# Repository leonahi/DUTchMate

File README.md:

<p align="center">
  Connect your coding agent to your embedded device.
</p>

# DUTchMate

DUTchMate gives your coding agent access to UART logs, firmware commands, and
configured reset and boot controls through MCP. Your agent can investigate
device behavior alongside your source code, using recorded evidence.

Use your coding agent's existing model. The separate DUTchMate Debug Agent
package is not required.

## 1. Install DUTchMate

Requires **Python 3.10+** and **uv**:

```bash
uv tool install dutchmate==0.2.0
```

If the installed commands are not on your PATH, run `uv tool update-shell` and
reopen your terminal. See the [v0.2.0 release notes](docs/releases/v0.2.0.md)
for upgrade guidance, or the [setup guide](docs/developer_guide.md#local-setup)
to run from a repository checkout.

## 2. Connect your device

| Connection | Available capabilities |
|---|---|
| TTL USB-to-UART adapter (Basic) | UART logs and optional firmware commands |
| RP2350 Pico 2 Debug Helper (Enhanced) | UART plus configured reset, boot and GPIO control |

Connect your adapter and configure the matching baud rate and wiring. See the
[setup guide](docs/developer_guide.md#local-setup) for configuration. Replace
`YOUR_UART_PORT` with your adapter's actual serial port:

```bash
dutchmate start --backend basic --serial-port YOUR_UART_PORT
dutchmate status
```

For the Debug Helper, use `dutchmate start --backend enhanced` instead. Follow
the [wiring guide](hardware/firmware/rp2350_debug_helper/README.md#revision-a-mapping)
to connect its DUT_VIO reference to the DUT's logic supply.

## 3. Connect your coding agent

Find the MCP launcher's absolute path:

```bash
command -v dutchmate-mcp
```

Register a local MCP server in your coding agent with these settings:

| Setting | Value |
|---|---|
| Name | `dutchmate` |
| Transport | `stdio` |
| Command | The absolute launcher path printed above |
| Arguments | `--service-url http://127.0.0.1:2040` |

See the [agent-specific configuration examples](docs/developer_guide.md#register-mcp-with-a-coding-agent)
for the format your host expects. Your coding agent launches the MCP process.
**The Device Core Service must already be running; MCP does not start it.**

Verify that the agent lists the DUTchMate tools, then ask it to check the device
connection before debugging.

## 4. Start debugging

Try these prompts in your coding agent:

> Check the device connection and summarize the latest UART logs.

> Observe UART for 15 seconds and identify errors or unexpected behavior.

> Investigate this boot failure using the UART evidence and this repository.
> Propose a fix, and ask before resetting the board or sending commands.

DUTchMate records UART continuously while the service owns the connection, so
your agent can retrieve evidence between requests. Sending commands requires
UART TX to be enabled; reset and boot actions require configured control mappings.

When finished:

```bash
dutchmate stop
```

## Further information

- [Configuration and CLI workflows](docs/developer_guide.md) — also run `dutchmate --help`.
- [Debug Helper wiring and firmware](hardware/firmware/rp2350_debug_helper/README.md).
- [Milestone overview and validation boundaries](docs/development_status.md).
- [Contributing](CONTRIBUTING.md) and the [documentation index](docs/README.md).

## Licensing

Software, firmware and documentation use the [MIT License](LICENSE), unless
otherwise noted. DUTchMate-authored hardware design files under `hardware/pcb/`
use [CERN-OHL-P-2.0](LICENSES/CERN-OHL-P-2.0.txt). Legacy EAGLE and third-party
assets retain their existing terms; see [LICENSE.md](LICENSE.md) and
[third-party notices](THIRD_PARTY_NOTICES.md).

The DUTchMate name, logo and branding are excluded from these grants; they do
not authorize presenting derivative products as official DUTchMate products.
Contributions require DCO 1.1 sign-off; see [CONTRIBUTING.md](CONTRIBUTING.md).

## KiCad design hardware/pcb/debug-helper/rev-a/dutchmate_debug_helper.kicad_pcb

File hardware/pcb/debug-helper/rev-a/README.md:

# Debug Helper Revision A — KiCad source

This directory contains the current authoritative Rev-A KiCad design source
for the DUTchMate Debug Helper. The historical EAGLE prototype design record
is preserved separately under [legacy-eagle](../legacy-eagle/revision_a.md).
Its component references and connector assignments do not define this KiCad
implementation.

## Design sources

- `dutchmate_debug_helper.kicad_pro`: KiCad project and check settings.
- `dutchmate_debug_helper.kicad_sch`: schematic and embedded symbol definitions.
- `dutchmate_debug_helper.kicad_pcb`: board source.
- `dutchmate_debug_helper.kicad_dru`: project design rules.
- `libraries/symbols/dutchmate.kicad_sym`: project-owned logic and analog-switch
  symbol definitions, resolved through `sym-lib-table` using `${KIPRJMOD}`.
- `libraries/symbols/third_party/snapeda.kicad_sym` and
  `libraries/footprints/third_party/snapeda.pretty/`: imported TPD4E05U06DQAR
  symbol and footprint, resolved through `sym-lib-table` and `fp-lib-table`.

The sources use KiCad 10 format. Standard KiCad symbols and footprints must be
installed alongside the project-owned library. Keep editable sources and any
reviewed manufacturing outputs in version control; local settings, locks,
autosaves, backups, and scratch exports are ignored.

## Electrical architecture and agreed corrections

The helper uses a non-wireless Raspberry Pi Pico 2 / RP2350 module (`A1`),
with a 3.3 V helper domain, a DUT-supplied `DUT_VIO` reference of 1.8–5.0 V,
and common ground. `DUT_VIO` supplies the interface circuitry; it is not an
output for powering the DUT.

| Block | KiCad implementation |
|---|---|
| Four control outputs | `U1 SN74LV4T125`, VCC=`DUT_VIO`; `U7/U8 SN74LVC2G06` open-drain enable drivers powered by `+3.3V` |
| Control data defaults | `R14–R17`, 10 kΩ to GND on `DBG_CTRL_DATA0–3` |
| Control enable defaults | `R1–R4`, 4.7 kΩ to GND; active-low `DBG_CTRL_OE0_N–3_N` pulled to `DUT_VIO` by `R7/R6/R9/R8`, respectively, each 4.7 kΩ |
| Four event inputs | `U5 TXU0104PWR`, VCCA=`DUT_VIO`, VCCB=`+3.3V`; `R5=4.7 kΩ` pulls `DBG_INPUT_IF_EN` low |
| UART | `U2 TXU0202DCUR`, VCCA=`+3.3V`, VCCB=`DUT_VIO`; `R12=4.7 kΩ` pulls `DBG_UART_IF_EN` low |
| Series resistance | `RN3/RN4=180 Ω` for control/event channels; `RN5=22 Ω` for UART |
| Protection | `U9 TPD4E05U06DQAR` on connector-side controls, `U4` on connector-side events/UART, `D1` between `DUT_VIO` and GND |

The 4.7 kΩ enable pull-downs retain compatibility with older RP2350 A2
silicon; the design does not require A4-only modules. Control data pull-downs
define the buffer inputs while Pico GPIOs are undriven. The independent `/OE`
paths determine DUT-facing Hi-Z, including open-drain release. Push-pull and
open-drain control modes still require the appropriate firmware data/enable
sequence.

### Hardware-defined DUT_VIO sense isolation

`U3 TMUX2819DSGR` is connected as follows:

| Pin | Connection |
|---|---|
| 1, SA | `DUT_VIO` |
| 2, NC | GND, as specified by the datasheet |
| 3, EN; 8, VDD | `+3.3V`, with `C16=100 nF` between VDD and GND |
| 4, GND; 9, exposed pad | GND |
| 5, SB | Intentionally unconnected |
| 6, D | `R10` divider input |
| 7, SEL | GND |

With helper power present, EN high and SEL low select SA. With VDD absent,
the switch provides powered-off isolation within its specified leakage limits.
No firmware GPIO controls this isolation. The selected switch supports DUT
signals above its 3.3 V supply within the specified signal range. See the
[TMUX2819 datasheet](https://www.ti.com/lit/ds/symlink/tmux2819.pdf).

The divider remains `R10=47 kΩ` and `R11=47 kΩ`, with `C7=10 nF` from
`DUT_VIO_SENSE` to `GNDA`. `R11` also returns to `GNDA`, connected to the
Pico's AGND pin 33. `DUT_VIO_SENSE` reaches GP28/ADC2, module pin 34. The Pico
module supplies the internal analog/common-ground connection; these are
distinct carrier-board net names, not galvanically isolated domains.

Normal helper startup disables GP28 digital input/output and internal pulls,
then releases the RP2350 pad-isolation latch so the reset pull cannot load the
divider. GP28 ADC sensing remains unimplemented: there is no ADC channel setup
or sampled voltage monitoring. The optional
[pad readback](../../../firmware/rp2350_debug_helper/README.md#gp28-sense-pin-initialization)
reports control bits without implementing sensing. Future ADC use must retain
the appropriate analog pin configuration. MCU pad isolation and U3's
hardware-defined powered-off isolation are separate paths; neither the
schematic nor the switch enable establishes firmware voltage measurements.

### UART receive bias

```text
J1.7 / DUT_UART_TX -- RN5A 22 Ω (pad 4 → pad 1) -- U2.B2 (pin 1)
                                                     |
                                                 R13 10 kΩ
                                                     |
                                                  DUT_VIO
```

`R13` is on the translator-input side of the series resistor, on exported net
`Net-(RN5A-R1.1)`. It references `DUT_VIO`, not fixed `+3.3V`. The translated
output is `DBG_UART_RX`, from U2 pin 4 to Pico GP1. The opposite direction is
Pico GP0 / `DBG_UART_TX` to U2 pin 5, U2 pin 8 through RN5B, then
`DUT_UART_RX` at J1 pin 8. Both UART directions share U2 OE; software TX
permission does not provide independent electrical TX isolation.

## DUT connector and interface requirements

The single 2×8 `J1` is the authoritative Rev-A DUT connector. Direct legacy
EAGLE harness compatibility is not required; any legacy connection requires
an external adapter cable.

| J1 pin(s) | Net(s) | Direction relative to helper |
|---|---|---|
| 1, 2 | GND | Common |
| 3, 4, 5, 6 | `DUT_CTRL0`, `DUT_CTRL1`, `DUT_CTRL2`, `DUT_CTRL3` | Outputs |
| 7 | `DUT_UART_TX` | Input from DUT TX |
| 8 | `DUT_UART_RX` | Output to DUT RX |
| 9, 10 | `DUT_EVENT2`, `DUT_EVENT3` | Inputs |
| 11, 12 | `DUT_EVENT0`, `DUT_EVENT1` | Inputs |
| 13 | GND | Common |
| 14 | `DUT_VIO` | Reference/supply input from DUT |
| 15, 16 | GND | Common |

`DUT_CTRL0–3` must remain within the `DUT_VIO` voltage domain. In particular,
a released externally pulled-up control signal must not be pulled above
`DUT_VIO`. U1 remains the selected SN74LV4T125. Control outputs drive logic
inputs, not DUT supply loads.

`DUT_EVENT0–3` intentionally have **no helper-side pull-ups**. These temporary
debugging inputs are normally driven by spare DUT GPIOs. The DUT/developer
must supply valid logic levels. Open-drain/open-collector outputs require a
DUT-side pull-up, including an MCU internal pull-up where its electrical and
timing performance is adequate. A floating event input is not a valid event
source.

## Validation lifecycle and evidence boundaries

The KiCad Rev-A schematic/source review is complete. PCB layout, routing,
fabrication preparation, DFM checks, Gerber review and manufacturing submission
are handled manually by the hardware designer outside the coding-agent
workflow. No further repository-driven PCB/DFM review task or acceptance gate
is planned before fabrication. Source-review completion does not establish
hardware acceptance, fabrication acceptance, production readiness or Phase 1B
acceptance.

Formal hardware validation of this corrected design begins only after
manufactured KiCad Rev-A PCBs are physically available. Each manufactured-board
validation campaign must record its own board/assembly configuration, wiring,
firmware, methods and observed results. Use the same broad categories as the
historical Rev-A work, adapted to this implementation, where applicable:

- Visual inspection, board assembly/continuity checks and firmware/board
  pin-mapping consistency.
- Power rails, `DUT_VIO` checks and operation across the supported voltage range.
- Debugger-powered/DUT-unpowered and DUT-powered/debugger-unpowered behavior,
  including powered-off back-power/leakage checks.
- `U3 TMUX2819` isolation of the `DUT_VIO` sense path and its divider/filter.
- Control-channel safe startup/Hi-Z, open-drain assertion/release and push-pull
  output levels.
- Event-input behavior with valid DUT-provided levels and any DUT-side pull-ups
  required for open-drain/open-collector signals.
- UART TX/RX functionality, the corrected after-RN5A `R13` pull-up, and UART
  signal-integrity/oscilloscope measurements.
- Hot-plug/unplug behavior and translator enable/disable sequencing.
- ESD/protection-path sanity checks where measurable, and Enhanced-backend HIL
  workflows relevant to the manufactured board.

These are future validation categories, not completed checks or new acceptance
criteria. Use applicable existing specifications and procedures for limits and
acceptance conditions; do not infer results or tolerances from source review.
The GP28 firmware limitation above and deferred EVENT capture must be respected
when defining what a physical run can demonstrate.

Adapt procedural references to the single 2×8 J1 pinout, current component/net
references and corrected circuit documented above. In particular, test the
after-RN5A `R13` pull-up at `U2.B2` to `DUT_VIO`; do not copy the historical
two-connector arrangement, historical R16 references or before-R16 rework
location into a KiCad-board procedure.

The three evidence scopes remain separate:

- Historical EAGLE [validation records](../../../validation/phase1_revision_a.md)
  establish evidence only for the actual EAGLE/as-built prototype, wiring,
  parts and firmware tested. They remain useful procedural/reference material.
  Their UART oscilloscope gap remains unresolved. The legacy board may still
  serve as a functional Enhanced HIL/development fixture under
  [Phase 1 specification §4.1](../../../../docs/specs/phase1_implementation_spec.md#41-software-sequencing-and-hardware-acceptance-boundaries);
  such use does not establish electrical acceptance. Current-board UART
  electrical follow-up belongs to the manufactured KiCad campaign above.
- The completed KiCad source review establishes that the corrected design
  source was reviewed; it is not physical-board validation.
- Future manufactured KiCad Rev-A validation supplies separate physical
  evidence required for that board. Historical acceptance is not inherited.

Current progress and the next formal hardware-validation step belong in
[development status](../../../../docs/development_status.md); dated decisions
and source-check results belong in
[development history](../../../../docs/development_history.md).

## Licensing and provenance

DUTchMate-authored design source, project metadata, and the project-owned
symbol definitions in this directory are licensed under
[CERN-OHL-P-2.0](../../../../LICENSES/CERN-OHL-P-2.0.txt).

Embedded and referenced third-party symbols, footprints, models, and other CAD
assets retain their existing terms. Standard KiCad library data retains its
upstream license and design exception. This grant does not establish ownership
of imported assets or complete the manufacturing-output provenance audit.
Do not copy embedded EAGLE libraries or other third-party CAD assets into this
project without checking their provenance and terms. See the
[hardware scope](../../README.md) and
[third-party notices](../../../../THIRD_PARTY_NOTICES.md).

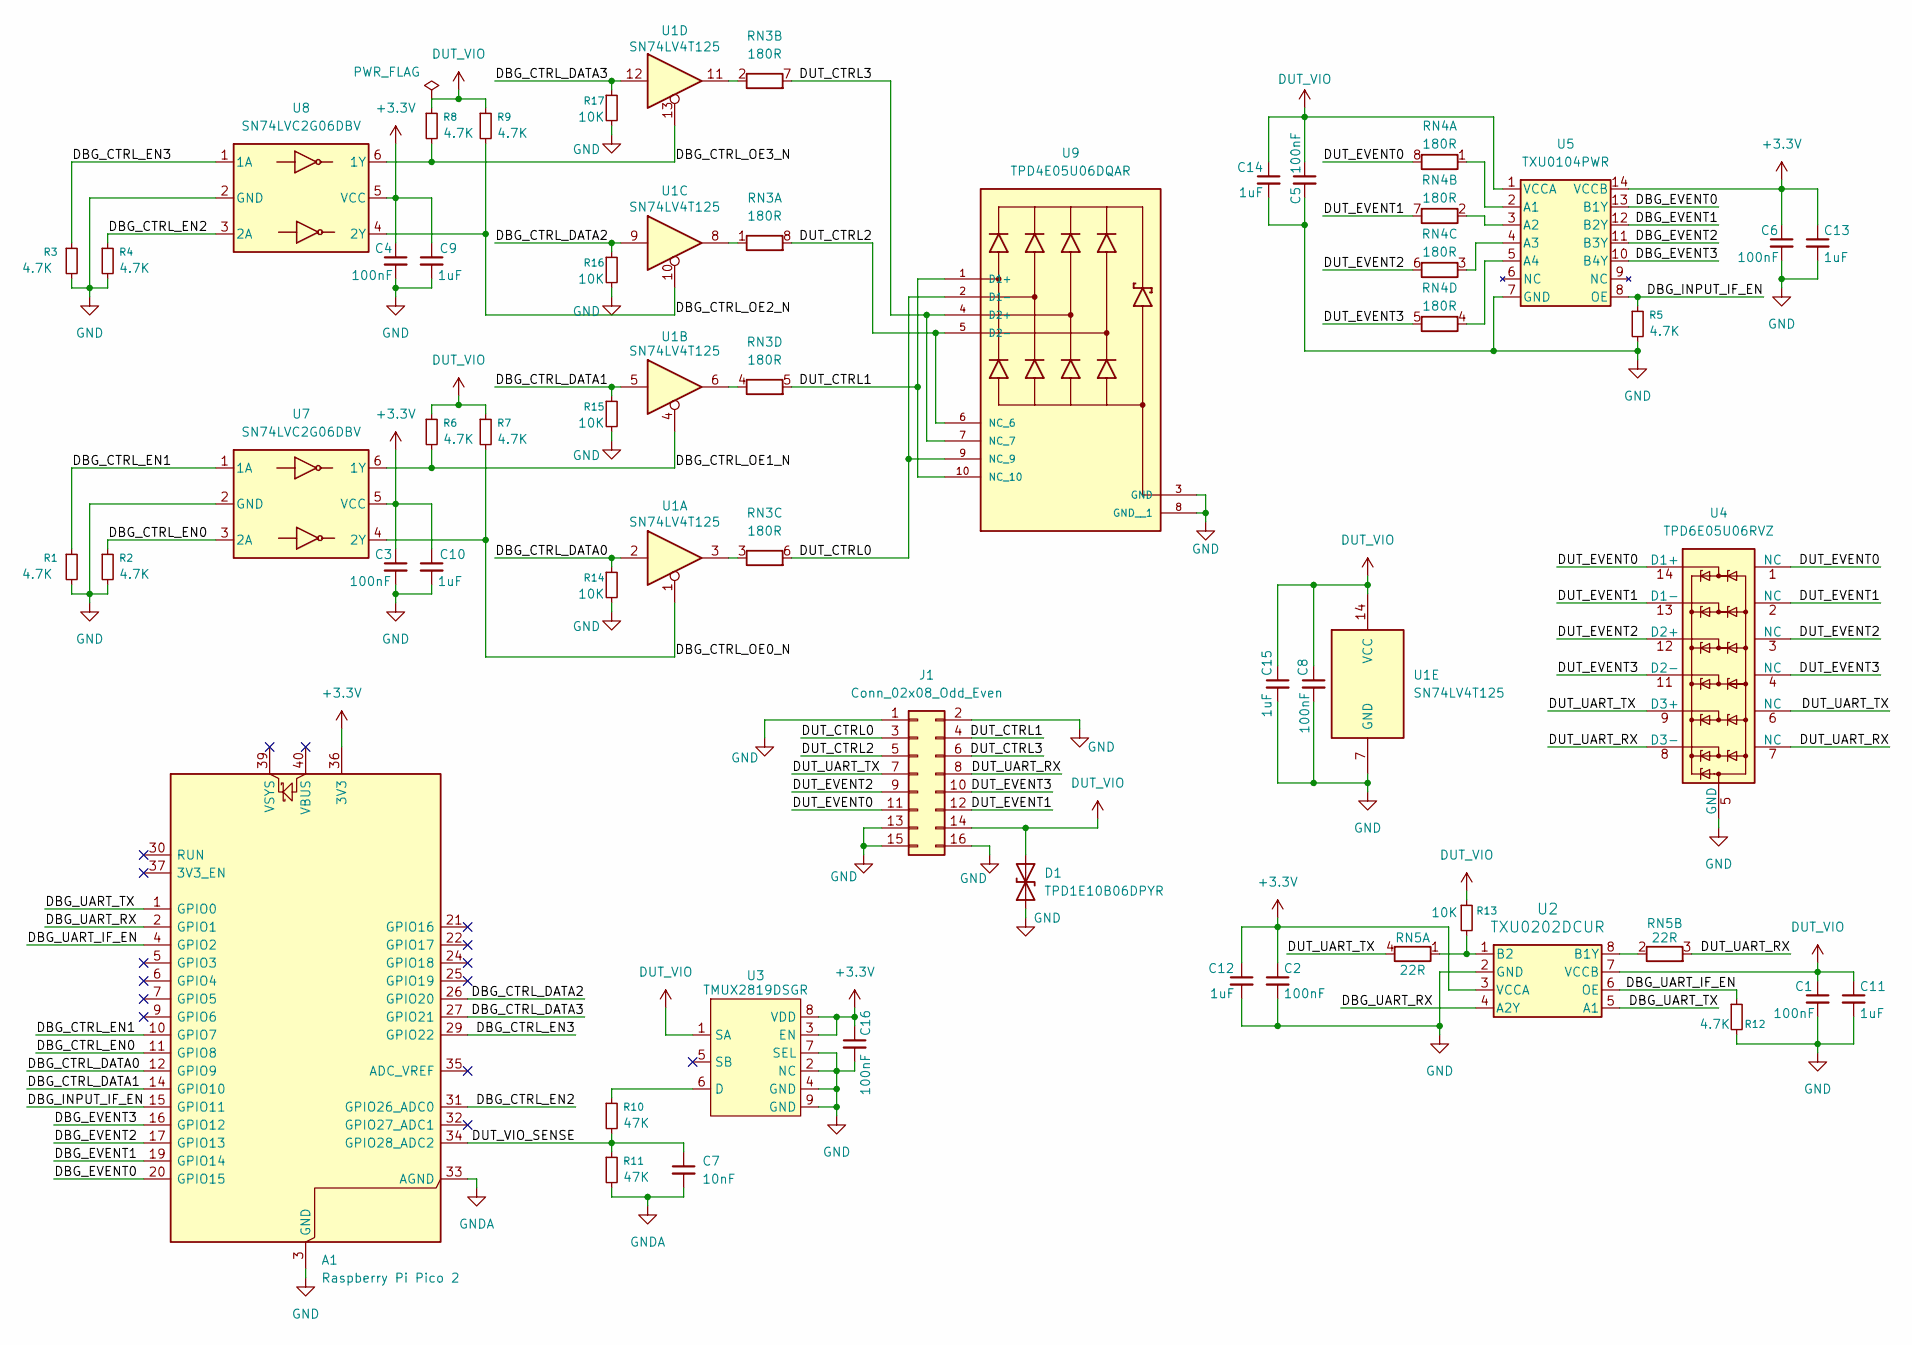
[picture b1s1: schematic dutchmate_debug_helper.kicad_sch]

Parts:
A1: Raspberry Pi Pico 2; RaspberryPi_Pico_Common_THT
C1, C2, C3, C4, C5, C6, C8, C16: 100nF; C_0603_1608Metric
C7: 10nF; C_0603_1608Metric
C9, C10, C11, C12, C13, C14, C15: 1uF; C_0603_1608Metric
D1: TPD1E10B06DPYR; Texas_DPY0002A_0.6x1mm_P0.65mm
J1: Conn_02x08_Odd_Even; PinHeader_2x08_P2.54mm_Vertical
R1, R2, R3, R4, R5, R6, R7, R8, R9, R12: 4.7K; R_0603_1608Metric
R10, R11: 47K; R_0603_1608Metric
R13, R14, R15, R16, R17: 10K; R_0603_1608Metric
RN3, RN4: 180R; R_Array_Concave_4x0603
RN5: 22R; R_Array_Concave_2x0603
U1: SN74LV4T125; TSSOP-14_4.4x5mm_P0.65mm
U2: TXU0202DCUR; VSSOP-8_2.3x2mm_P0.5mm
U3: TMUX2819DSGR; Texas_DSG0008A_WSON-8-1EP_2x2mm_P0.5mm_EP0.9x1.6mm
U4: TPD6E05U06RVZ; Texas_R-PUSON-N14
U5: TXU0104PWR; TSSOP-14_4.4x5mm_P0.65mm
U7, U8: SN74LVC2G06DBV; SOT-23-6
U9: TPD4E05U06DQAR; PARTREV N

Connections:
+3.3V: A1.36 (3V3), C2.1, C3.1, C4.1, C6.1, C9.1, C10.1, C12.1, C13.1, C16.1, U2.3 (VCCA), U3.3 (EN), U3.8 (VDD), U5.14 (VCCB), U7.5 (VCC), U8.5 (VCC)
/DBG_CTRL_DATA0: A1.12 (GPIO9), R14.1, U1.2
/DBG_CTRL_DATA1: A1.14 (GPIO10), R15.1, U1.5
/DBG_CTRL_DATA2: A1.26 (GPIO20), R16.1, U1.9
/DBG_CTRL_DATA3: A1.27 (GPIO21), R17.1, U1.12
/DBG_CTRL_EN0: A1.11 (GPIO8), R2.1, U7.3 (2A)
/DBG_CTRL_EN1: A1.10 (GPIO7), R1.1, U7.1 (1A)
/DBG_CTRL_EN2: A1.31 (GPIO26_ADC0), R4.1, U8.3 (2A)
/DBG_CTRL_EN3: A1.29 (GPIO22), R3.1, U8.1 (1A)
/DBG_CTRL_OE0_N: R7.2, U1.1, U7.4 (2Y)
/DBG_CTRL_OE1_N: R6.2, U1.4, U7.6 (1Y)
/DBG_CTRL_OE2_N: R9.2, U1.10, U8.4 (2Y)
/DBG_CTRL_OE3_N: R8.2, U1.13, U8.6 (1Y)
/DBG_EVENT0: A1.20 (GPIO15), U5.13 (B1Y)
/DBG_EVENT1: A1.19 (GPIO14), U5.12 (B2Y)
/DBG_EVENT2: A1.17 (GPIO13), U5.11 (B3Y)
/DBG_EVENT3: A1.16 (GPIO12), U5.10 (B4Y)
/DBG_INPUT_IF_EN: A1.15 (GPIO11), R5.1, U5.8 (OE)
/DBG_UART_IF_EN: A1.4 (GPIO2), R12.1, U2.6 (OE)
/DBG_UART_RX: A1.2 (GPIO1), U2.4 (A2Y)
/DBG_UART_TX: A1.1 (GPIO0), U2.5 (A1)
/DUT_CTRL0: J1.3, RN3.6 (R3.2), U9.2 (D1-), U9.9 (NC_9)
/DUT_CTRL1: J1.4, RN3.5 (R4.2), U9.1 (D1+), U9.10 (NC_10)
/DUT_CTRL2: J1.5, RN3.8 (R1.2), U9.5 (D2-), U9.6 (NC_6)
/DUT_CTRL3: J1.6, RN3.7 (R2.2), U9.4 (D2+), U9.7 (NC_7)
/DUT_EVENT0: J1.11, RN4.8 (R1.2), U4.1 (NC), U4.14 (D1+)
/DUT_EVENT1: J1.12, RN4.7 (R2.2), U4.2 (NC), U4.13 (D1-)
/DUT_EVENT2: J1.9, RN4.6 (R3.2), U4.3 (NC), U4.12 (D2+)
/DUT_EVENT3: J1.10, RN4.5 (R4.2), U4.4 (NC), U4.11 (D2-)
/DUT_UART_RX: J1.8, RN5.3 (R2.2), U4.7 (NC), U4.8 (D3-)
/DUT_UART_TX: J1.7, RN5.4 (R1.2), U4.6 (NC), U4.9 (D3+)
/DUT_VIO_SENSE: A1.34 (GPIO28_ADC2), C7.1, R10.2, R11.1
DUT_VIO: C1.1, C5.1, C8.1, C11.1, C14.1, C15.1, D1.2 (A2), J1.14, R6.1, R7.1, R8.1, R9.1, R13.1, U1.14 (VCC), U2.7 (VCCB), U3.1 (SA), U5.1 (VCCA)
GND: A1.3 (GND), A1.8 (GND), A1.13 (GND), A1.18 (GND), A1.23 (GND), A1.28 (GND), A1.38 (GND), C1.2, C2.2, C3.2, C4.2, C5.2, C6.2, C8.2, C9.2, C10.2, C11.2, C12.2, C13.2, C14.2, C15.2, C16.2, D1.1 (A1), J1.1, J1.2, J1.13, J1.15, J1.16, R1.2, R2.2, R3.2, R4.2, R5.2, R12.2, R14.2, R15.2, R16.2, R17.2, U1.7 (GND), U2.2 (GND), U3.2 (NC), U3.4 (GND), U3.7 (SEL), U3.9 (GND), U4.5 (GND), U4.10 (GND), U5.7 (GND), U7.2 (GND), U8.2 (GND), U9.3 (GND), U9.8 (GND__1)
GNDA: A1.33 (AGND), C7.2, R11.2
unnamed: RN3.1 (R1.1), U1.8
unnamed: RN3.2 (R2.1), U1.11
unnamed: RN3.3 (R3.1), U1.3
unnamed: RN3.4 (R4.1), U1.6
unnamed: RN4.1 (R1.1), U5.2 (A1)
unnamed: RN4.2 (R2.1), U5.3 (A2)
unnamed: RN4.3 (R3.1), U5.4 (A3)
unnamed: RN4.4 (R4.1), U5.5 (A4)
unnamed: R13.2, RN5.1 (R1.1), U2.1 (B2)
unnamed: RN5.2 (R2.1), U2.8 (B1Y)
unnamed: R10.1, U3.6 (D)

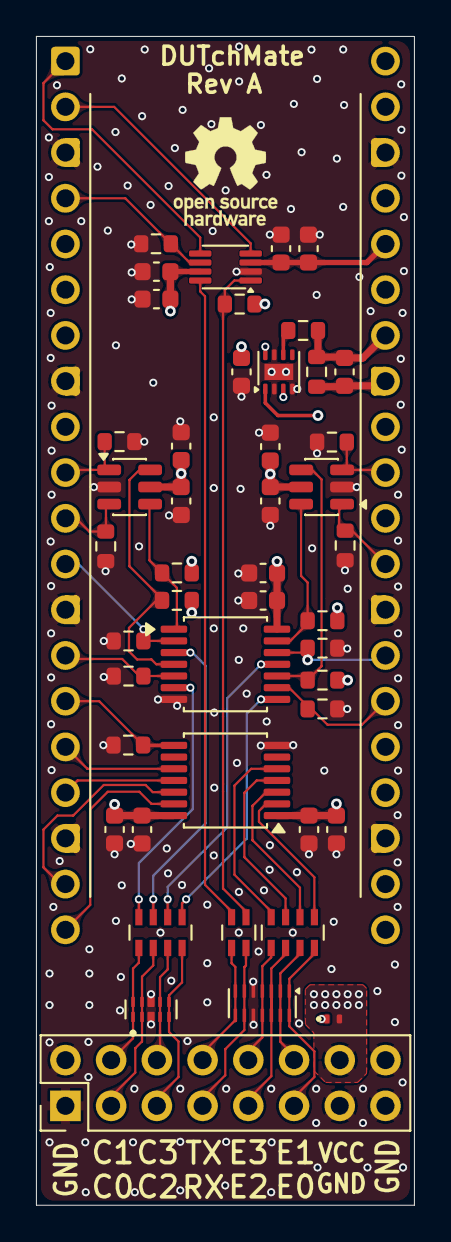
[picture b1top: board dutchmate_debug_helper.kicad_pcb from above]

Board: 4 copper layers, 21.0 x 64.9 mm, 47 parts (0 on the bottom side), 46 nets.
